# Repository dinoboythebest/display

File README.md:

# # Handheld RPG Console

## About the Project

The Handheld RPG Console is a small, custom-built gaming device designed to play a simple RPG using a Raspberry Pi Pico. The goal is to create a portable console with a screen, physical buttons, and custom hardware.

The console uses a Raspberry Pi Pico RP2040 as its main controller and a 1.54-inch ST7789 LCD display. The controls consist of six buttons: Up, Down, Left, Right, A, and B.

## How It Works

The Raspberry Pi Pico will read button inputs and use them to control the game. The directional buttons are used to move the player around the map, while A is used to interact with objects and B is used to open or close the inventory.

The RPG software is being developed in Python. Current game features include player movement, map boundaries, walls, treasure chests, an inventory system, health points, and turn-based battle mechanics.

The display will show the game, while the custom PCB will connect the Pico, screen, and buttons together.

## Hardware

- Raspberry Pi Pico RP2040
- 1.54-inch ST7789 LCD display (240 × 240)
- Six tactile buttons
- Custom-designed PCB
- USB connection for programming and power

## Controls

| Button | Function |
|---|---|
| Up | Move up / navigate menu |
| Down | Move down / navigate menu |
| Left | Move left |
| Right | Move right |
| A | Confirm / interact / attack |
| B | Open inventory / go back |

## Project Images

### PCB Design

### Display and Wiring

## Firmware

The game software is being developed in Python.

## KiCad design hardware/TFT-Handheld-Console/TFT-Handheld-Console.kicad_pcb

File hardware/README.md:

# Hardware

KiCad project files will go here.

No schematic or PCB has been completed yet. First verify the exact display module connector and pinout, then create the schematic and PCB in KiCad.

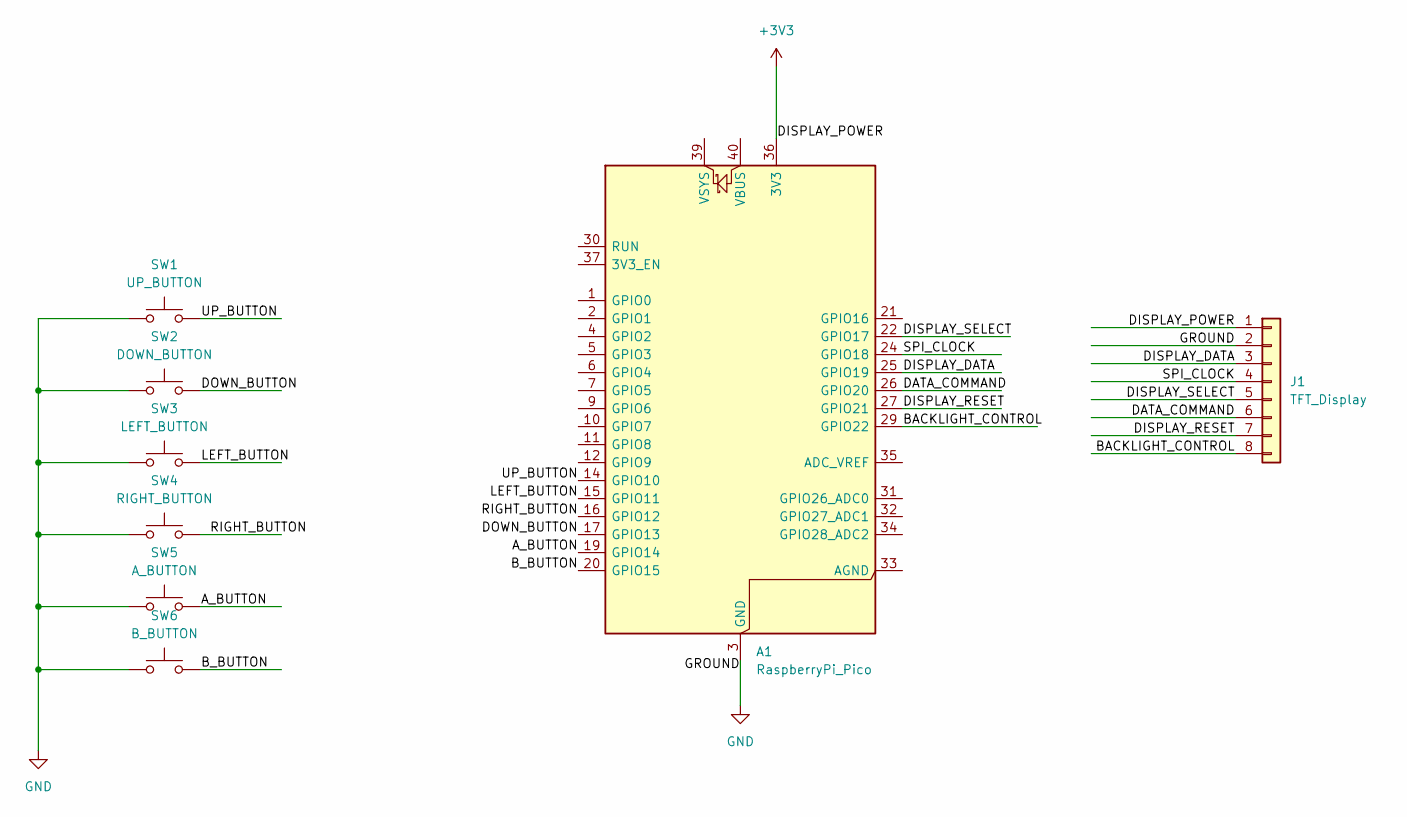
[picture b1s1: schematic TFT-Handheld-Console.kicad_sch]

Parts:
A1: RaspberryPi_Pico; RaspberryPi_Pico_Common_THT
J1: TFT_Display; JST_PH_B8B-PH-K_1x08_P2.00mm_Vertical
SW1: UP_BUTTON; SW_PUSH_6mm
SW2: DOWN_BUTTON; SW_PUSH_6mm
SW3: LEFT_BUTTON; SW_PUSH_6mm
SW4: RIGHT_BUTTON; SW_PUSH_6mm
SW5: A_BUTTON; SW_PUSH_6mm
SW6: B_BUTTON; SW_PUSH_6mm

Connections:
+3V3: A1.36 (3V3), J1.1
/A_BUTTON: A1.19 (GPIO14), SW5.2
/BACKLIGHT_CONTROL: A1.29 (GPIO22), J1.8
/B_BUTTON: A1.20 (GPIO15), SW6.2
/DATA_COMMAND: A1.26 (GPIO20), J1.6
/DISPLAY_DATA: A1.25 (GPIO19), J1.3
/DISPLAY_RESET: A1.27 (GPIO21), J1.7
/DISPLAY_SELECT: A1.22 (GPIO17), J1.5
/DOWN_BUTTON: A1.17 (GPIO13), SW2.2
/LEFT_BUTTON: A1.15 (GPIO11), SW3.2
/RIGHT_BUTTON: A1.16 (GPIO12), SW4.2
/SPI_CLOCK: A1.24 (GPIO18), J1.4
/UP_BUTTON: A1.14 (GPIO10), SW1.2
GND: A1.3 (GND), A1.8 (GND), A1.13 (GND), A1.18 (GND), A1.23 (GND), A1.28 (GND), A1.38 (GND), J1.2, SW1.1, SW2.1, SW3.1, SW4.1, SW5.1, SW6.1

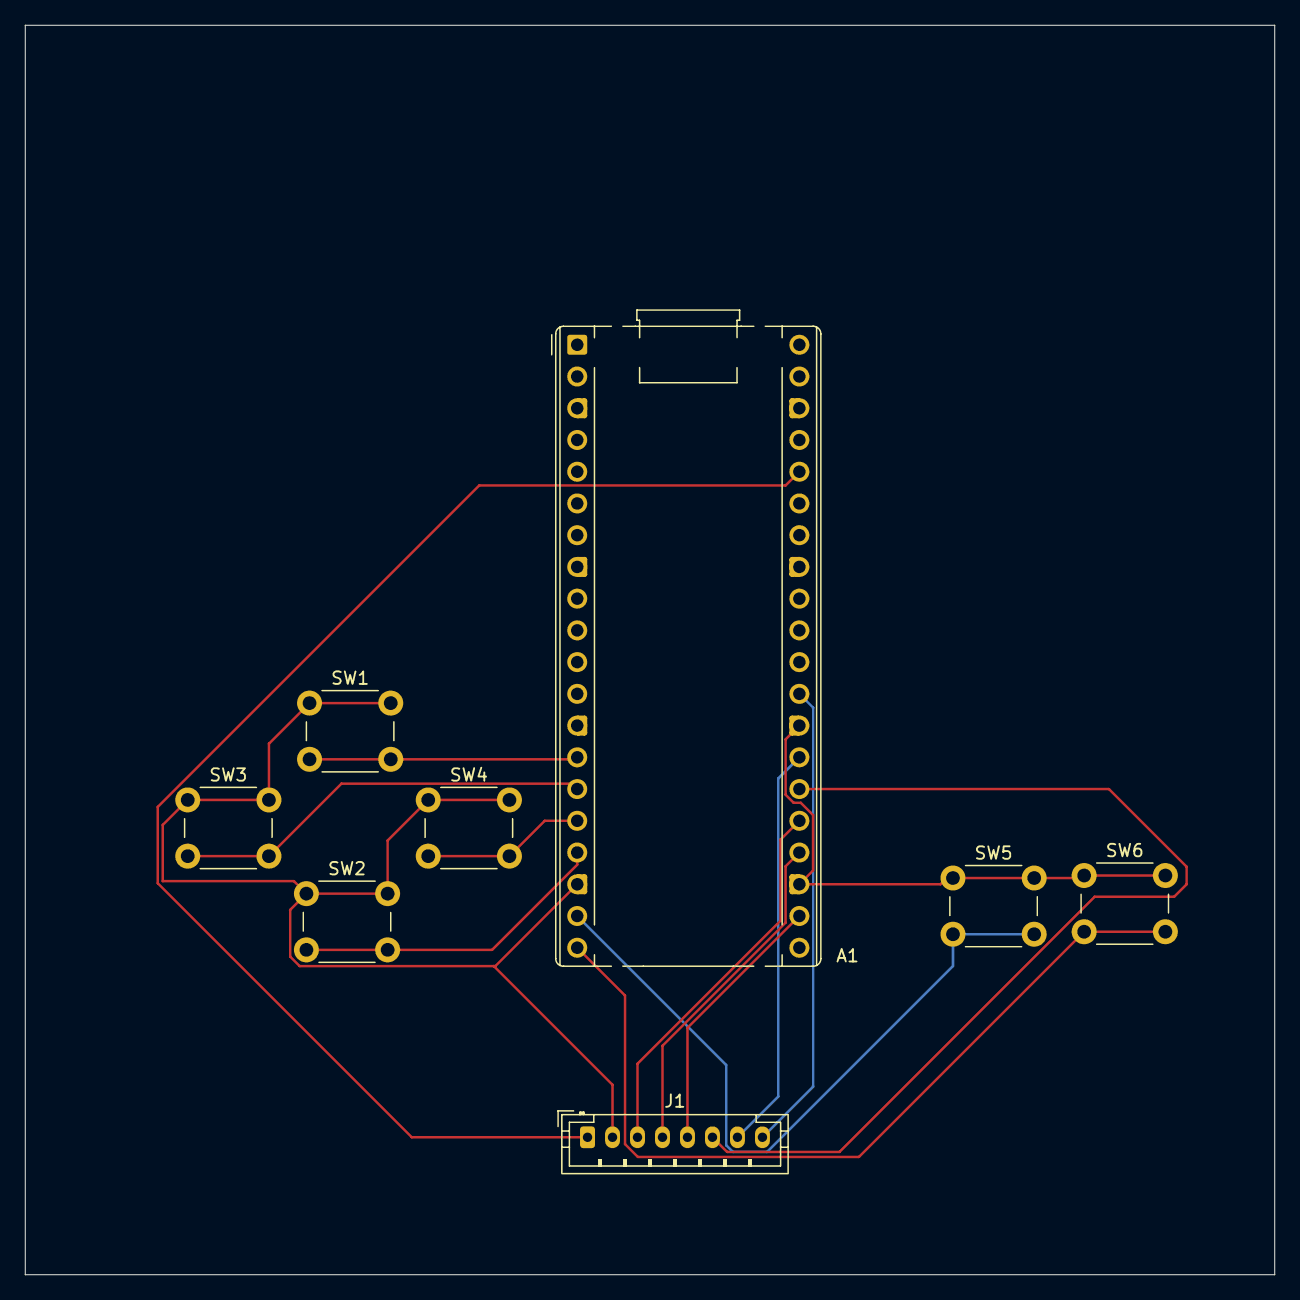
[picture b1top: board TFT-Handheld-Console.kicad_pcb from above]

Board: 2 copper layers, 100.0 x 100.0 mm, 8 parts (0 on the bottom side), 14 nets.
